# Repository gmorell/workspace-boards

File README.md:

# Gabe's Board Workspace

Kicad 7

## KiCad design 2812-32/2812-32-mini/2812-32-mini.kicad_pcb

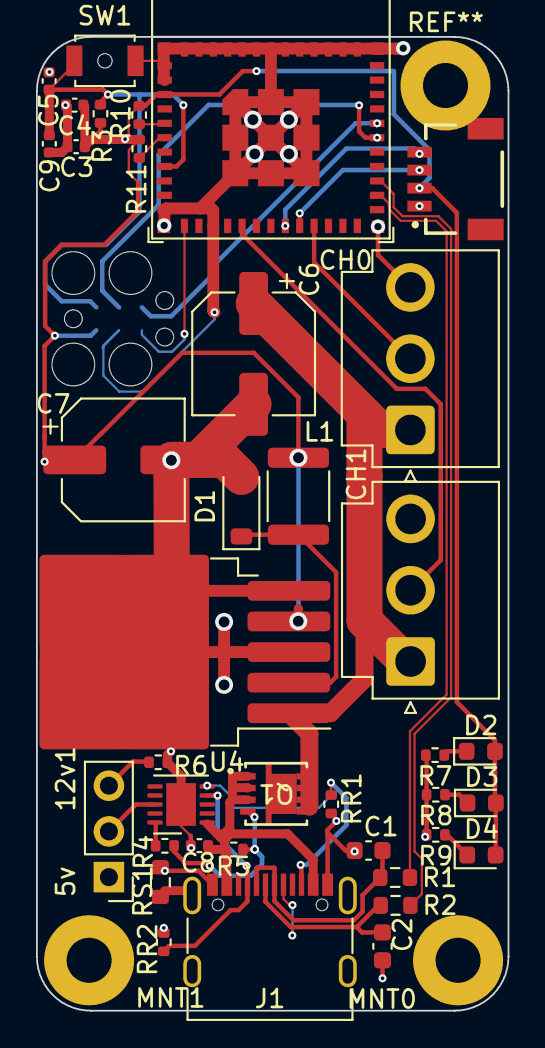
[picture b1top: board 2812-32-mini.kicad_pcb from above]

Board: 2 copper layers, 26.2 x 54.1 mm, 41 parts (1 on the bottom side), 29 nets.

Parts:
5v    12v1: VSEL; PinHeader_1x03_P2.54mm_Vertical
C1, C2: 47pF; C_0603_1608Metric
C3: 10uF; C_0402_1005Metric
C4, C9: 100nF; C_0402_1005Metric
C5, C8: 1uF; C_0402_1005Metric
C6: 100uF 50v; CP_Elec_6.3x5.3
C7: 330uF 16V; CP_Elec_6.3x7.7
CH0: CH0; JST_VH_B3P-VH-B_1x03_P3.96mm_Vertical
CH1: CH1; JST_VH_B3P-VH-B_1x03_P3.96mm_Vertical
D1: D_Schottky; D_SOD-123
D2, D3, D4: LED; LED_0603_1608Metric
J1: USB-C; USB_C_Receptacle_G-Switch_GT-USB-7010ASV
J2: I2C_STANDARDQWIIC; JST04_1MM_RA
L1: 330uH; L_1812_4532Metric
MNT0, MNT1: MountingHole_2.5mm_Pad
PROG1: TC2030-IDC_ESP; Tag-Connect_TC2030-IDC-FP_2x03_P1.27mm_Vertical
Q1: SI7611DN-T1-GE3; MOSFET_0DN-T1-GE3_VIS
R1, R2: 22; R_0603_1608Metric
R3, R6, R10, R11: 10k; R_0402_1005Metric
R4: 5.1K; R_0402_1005Metric
R5: 49.9K; R_0402_1005Metric
R7, R8, R9: R_US; R_0402_1005Metric
RR1, RR2: 5.1k; R_0402_1005Metric
RS1: 33K; R_0603_1608Metric
SW1: SW_DIP_x01; SW_SPST_B3U-1000P-B
U2: ESP32-C3-MINI-1
U3: LM2575-3.3BU; TO-263-5_TabPin3
U4: HUSB238; DFN-10-1EP_3x3mm_P0.5mm_EP1.65x2.38mm

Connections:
+3.3V: C3.1, C4.1, C7.1, D2.2 (A), D3.2 (A), D4.2 (A), J2.2 (VCC), L1.2, PROG1.2 (VDD), R3.2, R10.2, R11.2, U2.3 (3V3), U3.4 (FB)
D+: R2.2, U2.27 (GPIO19/USB_D+)
D-: R1.2, U2.26 (GPIO18/USB_D-)
EN: C5.2, C9.2, PROG1.1 (EN), R3.1, SW1.1, U2.8 (EN/CHIP_PU)
GND: 5v 12v1.1, C1.2, C2.2, C3.2, C4.2, C5.1, C6.2, C7.2, C8.2, C9.1, CH0.3, CH1.3, D1.2 (A), J1.A1 (GND), J1.A12 (GND), J1.B1 (GND), J1.B12 (GND), J2.1 (GND), PROG1.4 (GND), R6.2, R7.2, R8.2, R9.2, RR1.1, RR2.1, RS1.2, SW1.2, U2.1 (GND), U2.2 (GND), U2.11 (GND), U2.14 (GND), U2.36 (GND), U2.37 (GND), U2.38 (GND), U2.39 (GND), U2.40 (GND), U2.41 (GND), U2.42 (GND), U2.43 (GND), U2.44 (GND), U2.45 (GND), U2.46 (GND), U2.47 (GND), U2.48 (GND), U2.49 (GND), U2.50 (GND), U2.51 (GND), U2.52 (GND), U2.53 (GND), U3.3 (GND), U3.5 (~ON/OFF), U4.11 (GND)
GPIO0: PROG1.6 (IO0), U2.12 (GPIO0/ADC1_CH0/XTAL_32K_P)
GPIO7: CH0.2, U2.21 (GPIO7)
GPIO10: CH1.2, U2.16 (GPIO10)
unnamed: 5v 12v1.3, R6.1
unnamed: C1.1, J1.A7 (D-), J1.B7 (D-), R1.1
unnamed: C2.1, J1.A6 (D+), J1.B6 (D+), R2.1
unnamed: D1.1 (K), L1.1, U3.2 (OUT)
unnamed: D2.1 (K), R7.1
unnamed: D3.1 (K), R8.1
unnamed: D4.1 (K), R9.1
unnamed: J1.A5 (CC1), RR2.2, U4.4 (CC1)
unnamed: J1.B5 (CC2), RR1.2, U4.5 (CC2)
unnamed: J1.S1 (SHIELD), RS1.1
unnamed: Q1.4 (G), R4.1, R5.1
unnamed: R10.1, U2.5 (GPIO2/ADC1_CH2)
unnamed: R11.1, U2.6 (GPIO3/ADC1_CH3)
unnamed: R4.2, U4.10 (GATE)
unnamed: C8.1, J1.A4 (VBUS), J1.A9 (VBUS), J1.B4 (VBUS), J1.B9 (VBUS), Q1.1 (S), Q1.2 (S), Q1.3 (S), R5.2, U4.1 (VIN)
unnamed: 5v 12v1.2, U4.8 (VSET)
RX: PROG1.3 (TX), U2.30 (GPIO20/U0RXD)
SCL1: J2.4 (SCL), U2.19 (GPIO5/ADC2_CH0)
SDA1: J2.3 (SDA), U2.20 (GPIO6)
TX: PROG1.5 (RX), U2.31 (GPIO21/U0TXD)
VDC: C6.1, CH0.1, CH1.1, Q1.5 (D), Q1.6 (D), Q1.7 (D), Q1.8 (D), U3.1 (VIN)

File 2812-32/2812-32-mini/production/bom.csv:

Designator,Footprint,Quantity,Value,LCSC Part #
5v    12v1,PinHeader_1x03_P2.54mm_Vertical,1,VSEL,C20607074
"C1, C2",0603,2,47pF,C1671
C3,0402,1,10uF,C15525
"C4, C9",0402,2,100nF,C307331
"C5, C8",0402,2,1uF,C20539426
C6,CP_Elec_6.3x5.3,1,100uF 50v,C5354996
C7,CP_Elec_6.3x7.7,1,330uF 16V,C2980164
CH0,JST_VH_B3P-VH-B_1x03_P3.96mm_Vertical,1,CH0,C265360
CH1,JST_VH_B3P-VH-B_1x03_P3.96mm_Vertical,1,CH1,C265360
D1,D_SOD-123,1,D_Schottky,C437199
"D2, D3, D4",0603,3,LED,C5656657
J1,USB_C_Receptacle_G-Switch_GT-USB-7010ASV,1,USB-C,C2988369
J2,JST04_1MM_RA,1,I2C_STANDARDQWIIC,C160404
L1,1812,1,330uH,C394139
PROG1,Tag-Connect_TC2030-IDC-FP_2x03_P1.27mm_Vertical,1,TC2030-IDC_ESP,
Q1,MOSFET_0DN-T1-GE3_VIS,1,SI7611DN-T1-GE3,C141542
"R1, R2",0603,2,22,C2930077
"R10, R11, R3, R6",0402,4,10k,C25744
"R4, RR1, RR2",0402,3,5.1K,C25905
R5,0402,1,49.9K,C409918
"R7, R8, R9",0402,3,R_US,C2906961
RS1,0603,1,33K,C4216
SW1,SW_SPST_B3U-1000P-B,1,SW_DIP_x01,C231329
U2,ESP32-C3-MINI-1,1,ESP32-C3-MINI-1,C2838502
U3,TO-263-5_TabPin3,1,LM2575-3.3BU,C2977107
U4,DFN-10-1EP_3x3mm_P0.5mm_EP1.65x2.38mm,1,HUSB238,C7471904

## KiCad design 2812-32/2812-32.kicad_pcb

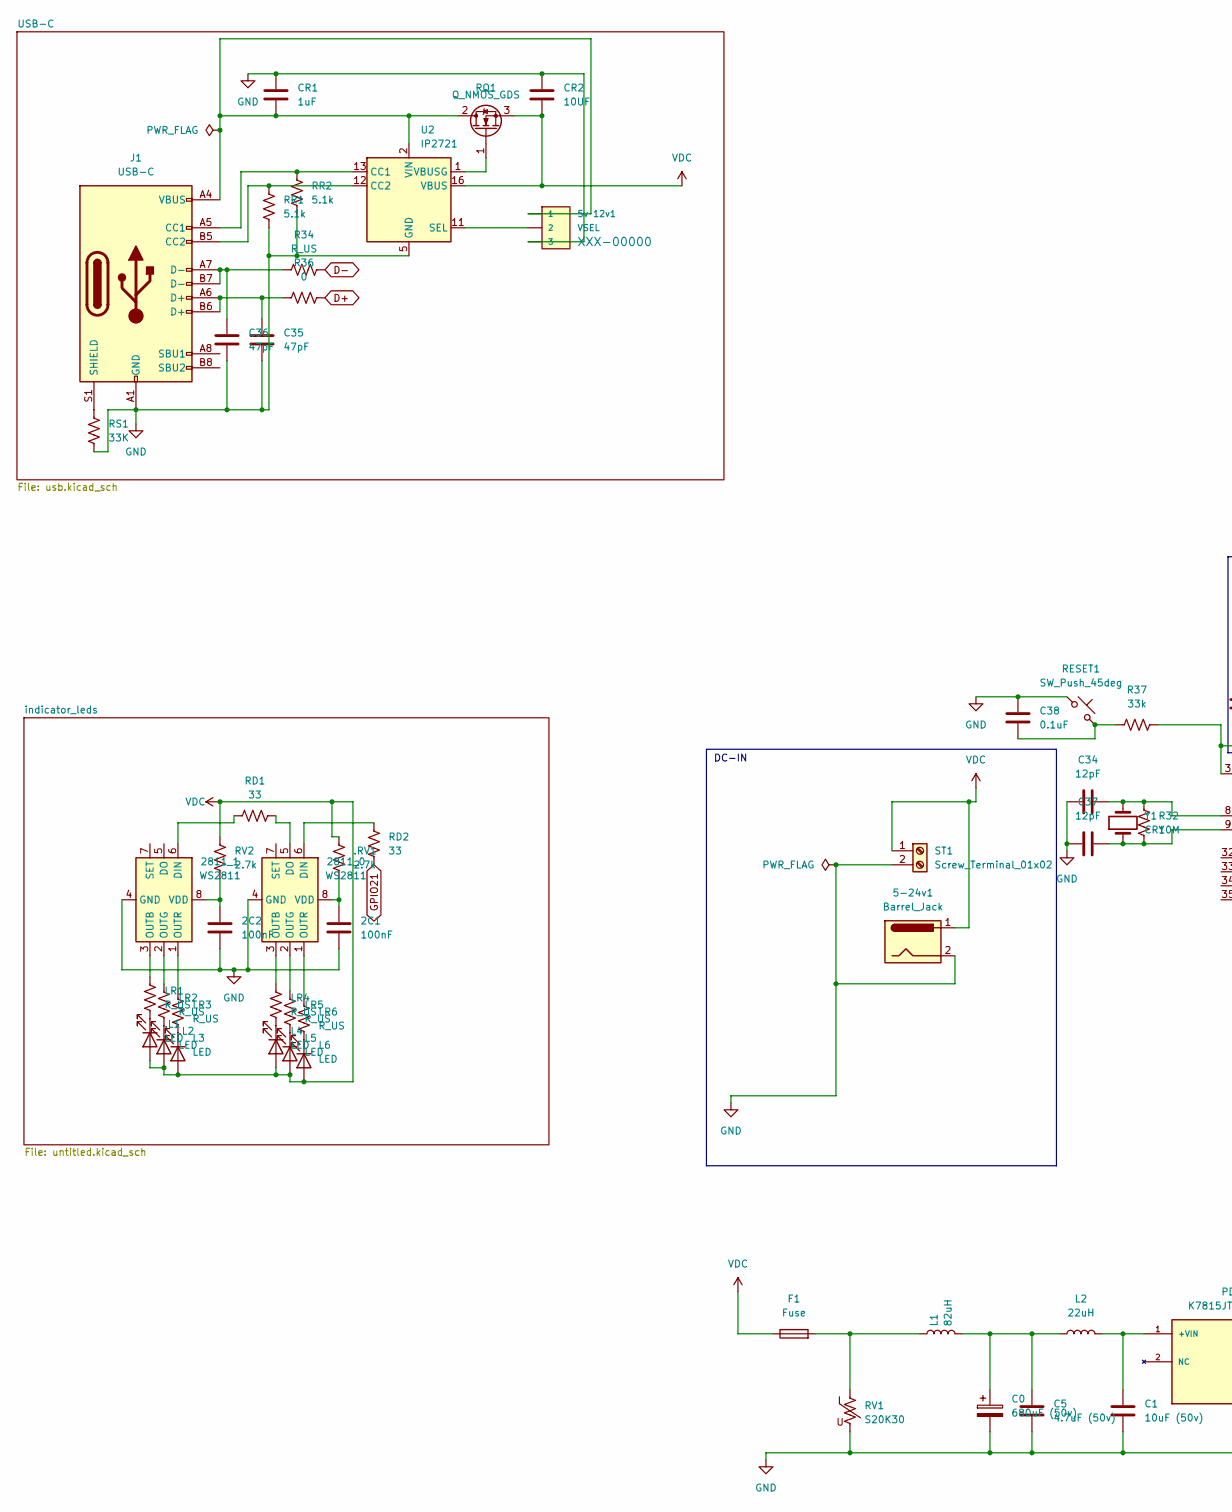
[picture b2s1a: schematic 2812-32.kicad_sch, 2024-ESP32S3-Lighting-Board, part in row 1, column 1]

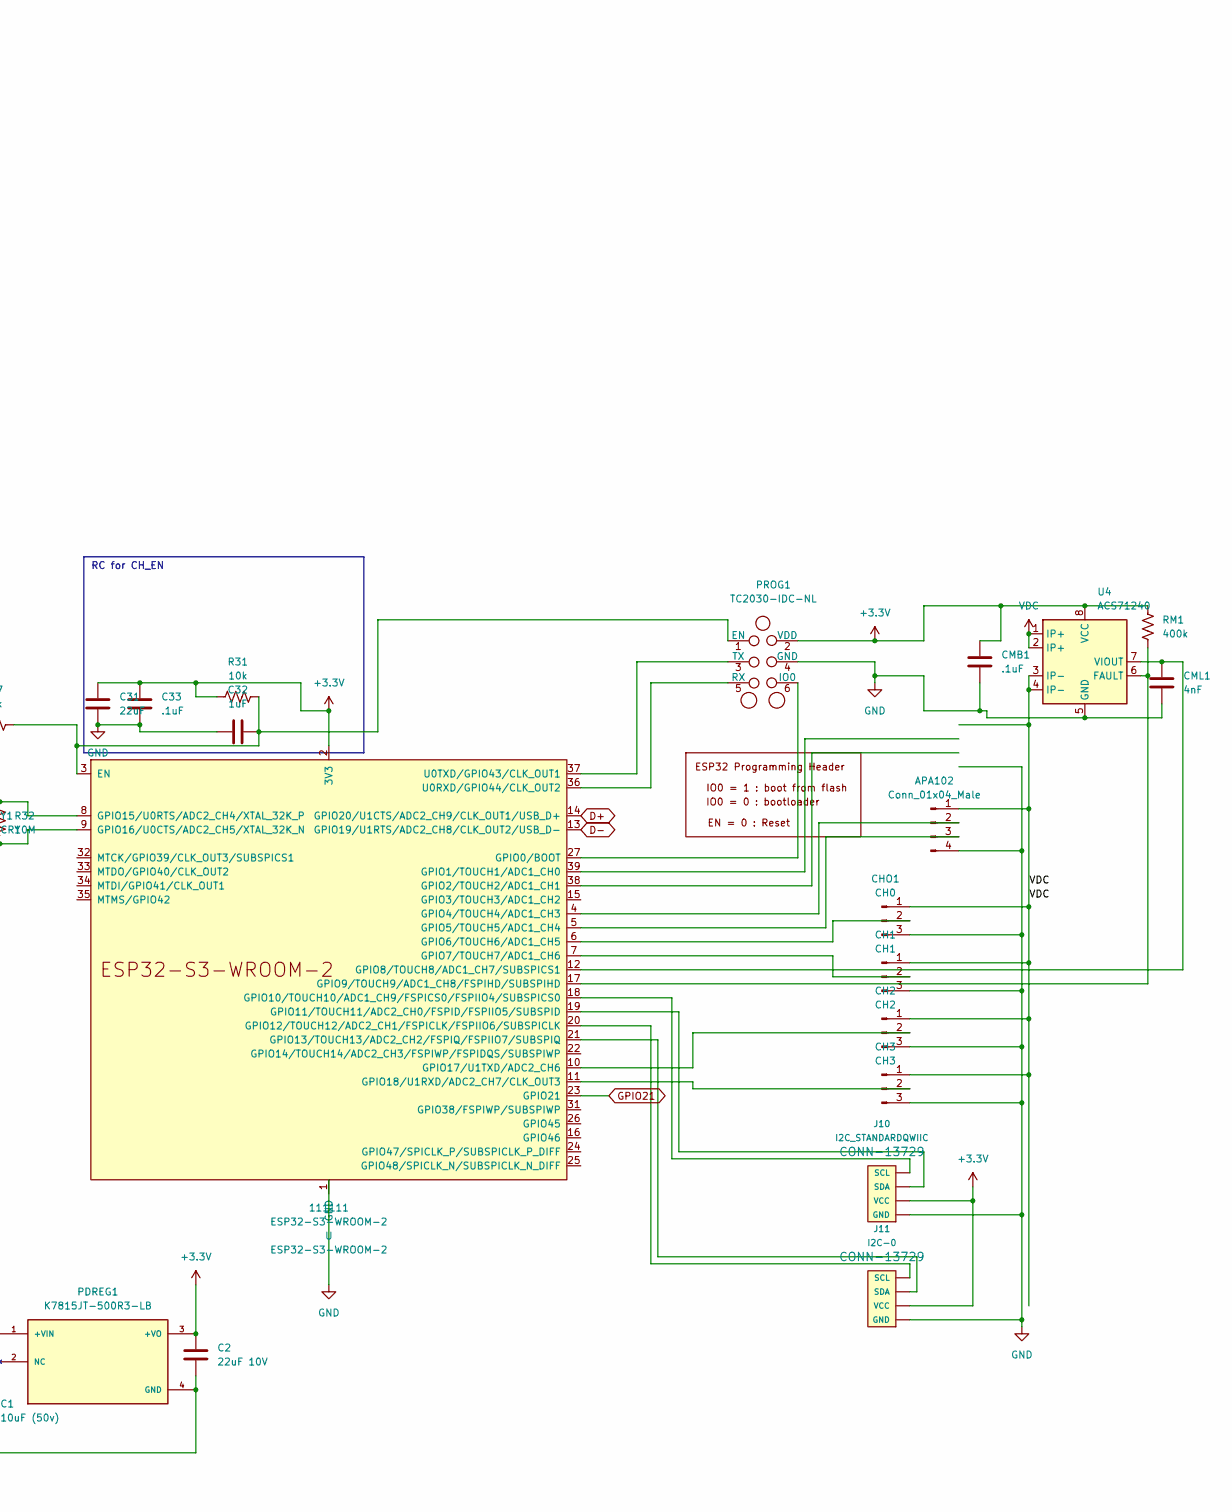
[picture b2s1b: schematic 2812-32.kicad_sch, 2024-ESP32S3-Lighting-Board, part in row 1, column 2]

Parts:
2C1, 2C2: 100nF; C_0603_1608Metric
5-24v1: Barrel_Jack; BarrelJack_CUI_PJ-063AH_Horizontal
5v    12v1: VSEL; PinHeader_1x03_P2.54mm_Vertical
2811_0, 2811_1: WS2811; SOP-8_3.9x4.9mm_P1.27mm
111111: ESP32-S3-WROOM-2
.L1, .L2: LED; LED_0603_1608Metric
.RV1: 2.7k; R_0603_1608Metric
APA102: Conn_01x04_Male; JST_VH_B4PS-VH_1x04_P3.96mm_Horizontal
C0: 680uF (50v); C_0603_1608Metric
C1: 10uF (50v); C_0603_1608Metric
C2: 22uF 10V; C_0603_1608Metric
C5: 4.7uF (50v); C_0603_1608Metric
C31: 22uF; C_0402_1005Metric
C32: 1uF; C_0603_1608Metric
C33: .1uF; C_0603_1608Metric
C34, C37: 12pF; C_0603_1608Metric
C35, C36: 47pF; C_0603_1608Metric
C38: 0.1uF; C_0603_1608Metric
CH1: CH1; JST_VH_B3PS-VH_1x03_P3.96mm_Horizontal
CH2: CH2; JST_VH_B3PS-VH_1x03_P3.96mm_Horizontal
CH3: CH3; JST_VH_B3PS-VH_1x03_P3.96mm_Horizontal
CHO1: CH0; JST_VH_B3PS-VH_1x03_P3.96mm_Horizontal
CMB1: .1uF; C_0402_1005Metric
CML1: 4nF; C_0402_1005Metric
CR1: 1uF; C_0402_1005Metric
CR2: 10UF; C_0402_1005Metric
F1: Fuse; Fuse_0603_1608Metric
J1: USB-C; USB_C_Receptacle_G-Switch_GT-USB-7010ASV
J10: I2C_STANDARDQWIIC; JST04_1MM_RA
J11: I2C-0; JST04_1MM_RA
L1: 82uH; L_0603_1608Metric
L2: 22uH; L_0603_1608Metric
L3, L4, L5, L6: LED; LED_0603_1608Metric
LR1, LR2, LR3, LR4, LR5, LR6: R_US; R_0402_1005Metric
PDREG1: K7815JT-500R3-LB; CONV_K7815JT-500R3-LB; PARTREV 2022.07.25-A/4
PROG1: TC2030-IDC_ESP; Tag-Connect_TC2030-IDC-FP_2x03_P1.27mm_Vertical
R31: 10k; R_0603_1608Metric
R32: 10M; R_0603_1608Metric
R34: R_US; R_0603_1608Metric
R36: 0; R_0603_1608Metric
R37: 33k; R_0603_1608Metric
RD1, RD2: 33; R_0603_1608Metric
RESET1: SW_Push_45deg; SW_SPST_B3U-3000P-B
RM1: 400k; R_0402_1005Metric
RQ1: Q_NMOS_GDS; SOT-23
RR1, RR2: 5.1k; R_0402_1005Metric
RS1: 33K; R_0603_1608Metric
RV1: S20K30; RV_Disc_D9mm_W3.5mm_P5mm
RV2: 2.7k; R_0603_1608Metric
ST1: Screw_Terminal_01x02; TerminalBlock_MetzConnect_Type086_RT03402HBLC_1x02_P3.81mm_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
U2: IP2721; TSSOP-16_4.4x5mm_P0.65mm
U4: ACS71240; SOIC-8_3.9x4.9mm_P1.27mm
Y1: CRY; Crystal_SMD_MicroCrystal_CC8V-T1A-2Pin_2.0x1.2mm

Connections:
+3.3V: 111111.2 (3V3), C2.1, C31.1, C33.1, CMB1.1, J10.2 (VCC), J11.2 (VCC), PDREG1.3 (+VO), PROG1.2 (VDD), R31.1, RM1.2, U4.8 (VCC)
D+: 111111.14 (GPIO20/U1CTS/ADC2_CH9/CLK_OUT1/USB_D+), R36.2
D-: 111111.13 (GPIO19/U1RTS/ADC2_CH8/CLK_OUT2/USB_D-), R34.2
GND: 2C1.2, 2C2.2, 5-24v1.2, 5v 12v1.3, 2811_0.4 (GND), 2811_1.4 (GND), 111111.1 (GND), 111111.40 (GND), 111111.41 (GND), APA102.4, C0.2, C1.2, C2.2, C5.2, C31.2, C32.1, C33.2, C34.1, C35.2, C36.2, C37.1, C38.1, CH1.3, CH2.3, CH3.3, CHO1.3, CMB1.2, CML1.2, CR1.1, CR2.1, J1.A1 (GND), J1.A12 (GND), J1.B1 (GND), J1.B12 (GND), J10.1 (GND), J11.1 (GND), PDREG1.4 (GND), PROG1.4 (GND), RESET1.1, RR1.1, RR2.1, RS1.2, RV1.2, ST1.2, U2.5 (GND), U4.5 (GND)
GPIO21: 111111.23 (GPIO21), RD2.1
unnamed: 2811_0.6 (DIN), RD2.2
unnamed: 2811_0.5 (DO), RD1.2
unnamed: 2811_0.3 (OUTB), LR4.1
unnamed: 2811_0.2 (OUTG), LR5.1
unnamed: 2811_0.1 (OUTR), LR6.1
unnamed: 2C1.1, 2811_0.8 (VDD), .RV1.2
unnamed: 2811_1.6 (DIN), RD1.1
unnamed: 2811_1.3 (OUTB), LR1.1
unnamed: 2811_1.2 (OUTG), LR2.1
unnamed: 2811_1.1 (OUTR), LR3.1
unnamed: 2C2.1, 2811_1.8 (VDD), RV2.2
unnamed: 111111.3 (EN), C32.2, PROG1.1 (EN), R31.2, R37.2
unnamed: 111111.27 (GPIO0/BOOT), PROG1.6 (IO0)
unnamed: 111111.4 (GPIO4/TOUCH4/ADC1_CH3), APA102.2
unnamed: 111111.5 (GPIO5/TOUCH5/ADC1_CH4), APA102.3
unnamed: 111111.6 (GPIO6/TOUCH6/ADC1_CH5), CHO1.2
unnamed: 111111.7 (GPIO7/TOUCH7/ADC1_CH6), CH1.2
unnamed: 111111.12 (GPIO8/TOUCH8/ADC1_CH7/SUBSPICS1), CML1.1, U4.7 (VIOUT)
unnamed: 111111.17 (GPIO9/TOUCH9/ADC1_CH8/FSPIHD/SUBSPIHD), RM1.1, U4.6 (FAULT)
unnamed: 111111.18 (GPIO10/TOUCH10/ADC1_CH9/FSPICS0/FSPIIO4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), J10.4 (SCL)
unnamed: 111111.19 (GPIO11/TOUCH11/ADC2_CH0/FSPID/FSPIIO5/S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), J10.3 (SDA)
unnamed: 111111.20 (GPIO12/TOUCH12/ADC2_CH1/FSPICLK/FSPIIO6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), J11.4 (SCL)
unnamed: 111111.21 (GPIO13/TOUCH13/ADC2_CH2/FSPIQ/FSPIIO7/S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), J11.3 (SDA)
unnamed: 111111.8 (GPIO15/U0RTS/ADC2_CH4/XTAL_32K_P), C34.2, R32.1, Y1.2
unnamed: 111111.9 (GPIO16/U0CTS/ADC2_CH5/XTAL_32K_N), C37.2, R32.2, Y1.1
unnamed: 111111.10 (GPIO17/U1TXD/ADC2_CH6), CH2.2
unnamed: 111111.11 (GPIO18/U1RXD/ADC2_CH7/CLK_OUT3), CH3.2
unnamed: 111111.36 (U0RXD/GPIO44/CLK_OUT2), PROG1.5 (RX)
unnamed: 111111.37 (U0TXD/GPIO43/CLK_OUT1), PROG1.3 (TX)
unnamed: .L1.1 (K), LR1.2
unnamed: .L2.1 (K), LR2.2
unnamed: C0.1, C5.1, L1.2, L2.1
unnamed: C35.1, J1.A6 (D+), J1.B6 (D+), R36.1
unnamed: C36.1, J1.A7 (D-), J1.B7 (D-), R34.1
unnamed: C38.2, R37.1, RESET1.2
unnamed: F1.2, L1.1, RV1.1
unnamed: J1.A5 (CC1), RR2.2, U2.13 (CC1)
unnamed: J1.B5 (CC2), RR1.2, U2.12 (CC2)
unnamed: J1.S1 (SHIELD), RS1.1
unnamed: L3.1 (K), LR3.2
unnamed: L4.1 (K), LR4.2
unnamed: L5.1 (K), LR5.2
unnamed: L6.1 (K), LR6.2
unnamed: C1.1, L2.2, PDREG1.1 (+VIN)
unnamed: 5v 12v1.1, CR1.2, J1.A4 (VBUS), J1.A9 (VBUS), J1.B4 (VBUS), J1.B9 (VBUS), RQ1.2 (D), U2.2 (VIN)
unnamed: RQ1.1 (G), U2.1 (VBUSG)
unnamed: 5v 12v1.2, U2.11 (SEL)
VDC: 5-24v1.1, .L1.2 (A), .L2.2 (A), .RV1.1, APA102.1, CH1.1, CH2.1, CH3.1, CHO1.1, CR2.2, F1.1, L3.2 (A), L4.2 (A), L5.2 (A), L6.2 (A), RQ1.3 (S), RV2.1, ST1.1, U2.16 (VBUS), U4.1 (IP+), U4.2 (IP+), U4.3 (IP-), U4.4 (IP-)

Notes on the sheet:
DC-IN
RC for CH_EN

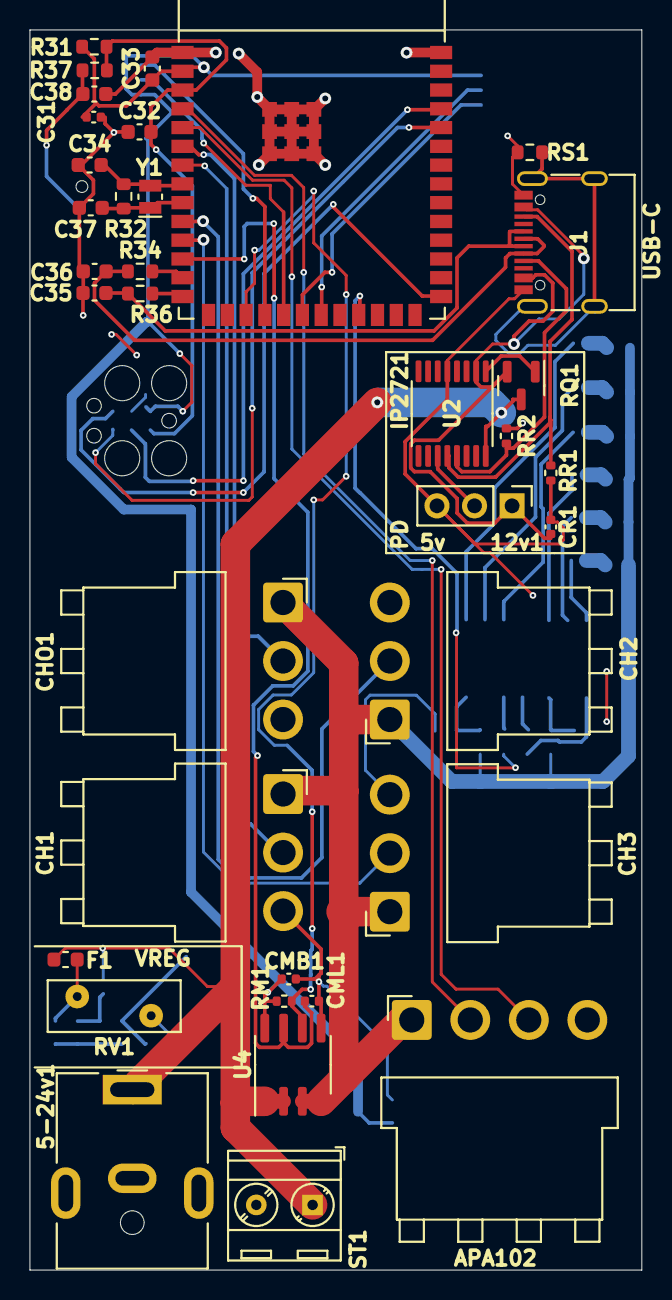
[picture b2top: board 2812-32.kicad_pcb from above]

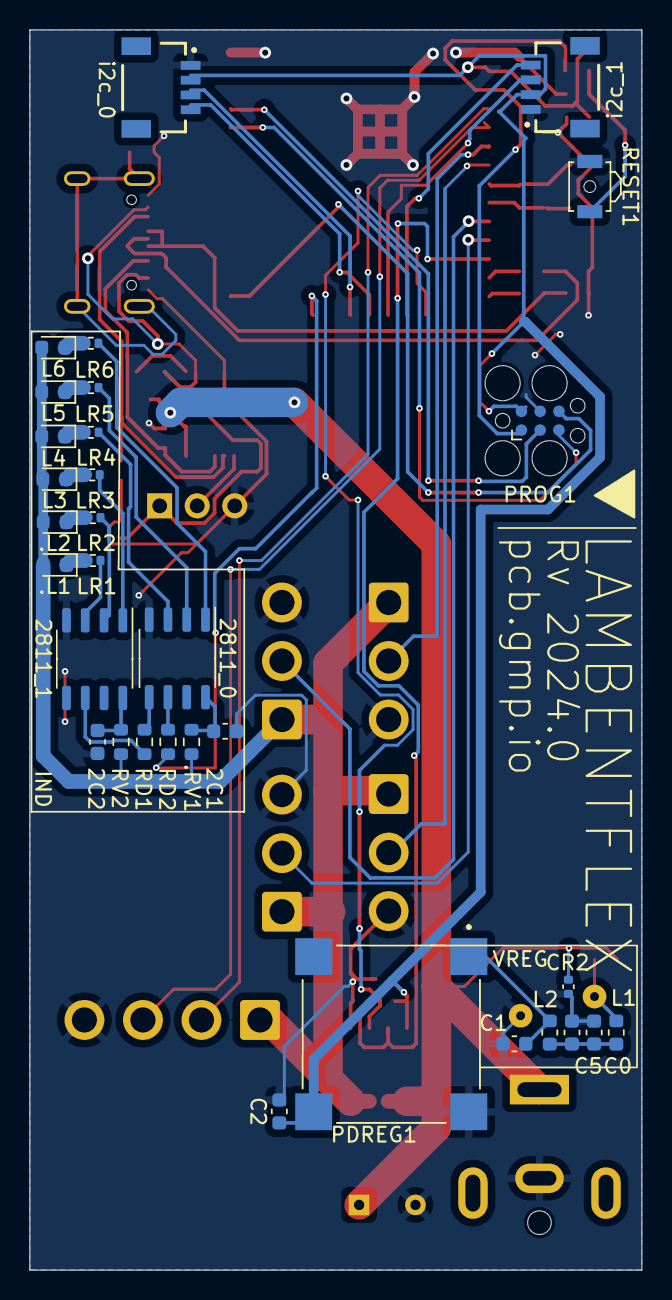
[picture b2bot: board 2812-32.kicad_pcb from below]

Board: 2 copper layers, 41.4 x 83.9 mm, 68 parts (32 on the bottom side), 53 nets.

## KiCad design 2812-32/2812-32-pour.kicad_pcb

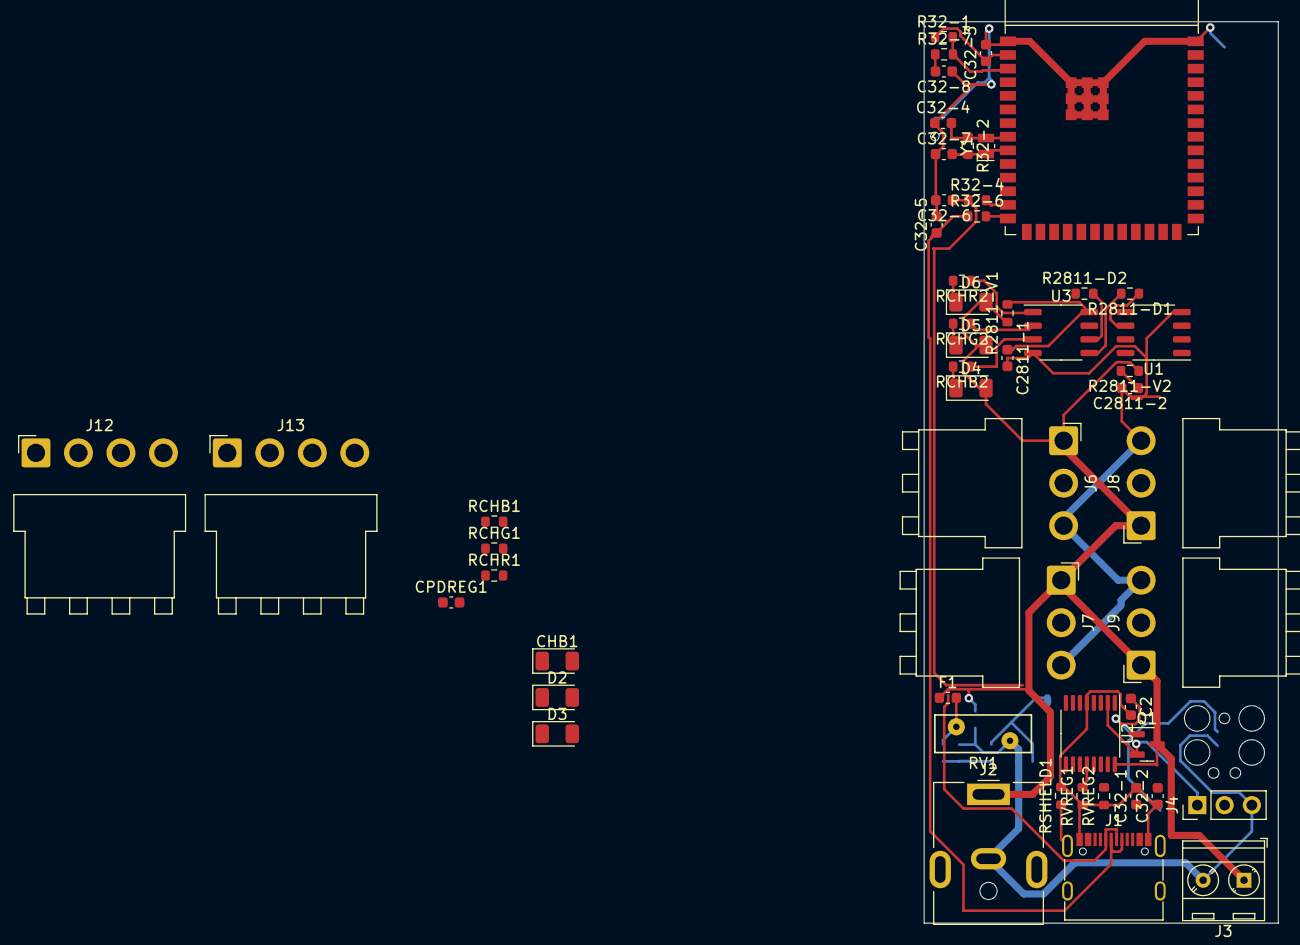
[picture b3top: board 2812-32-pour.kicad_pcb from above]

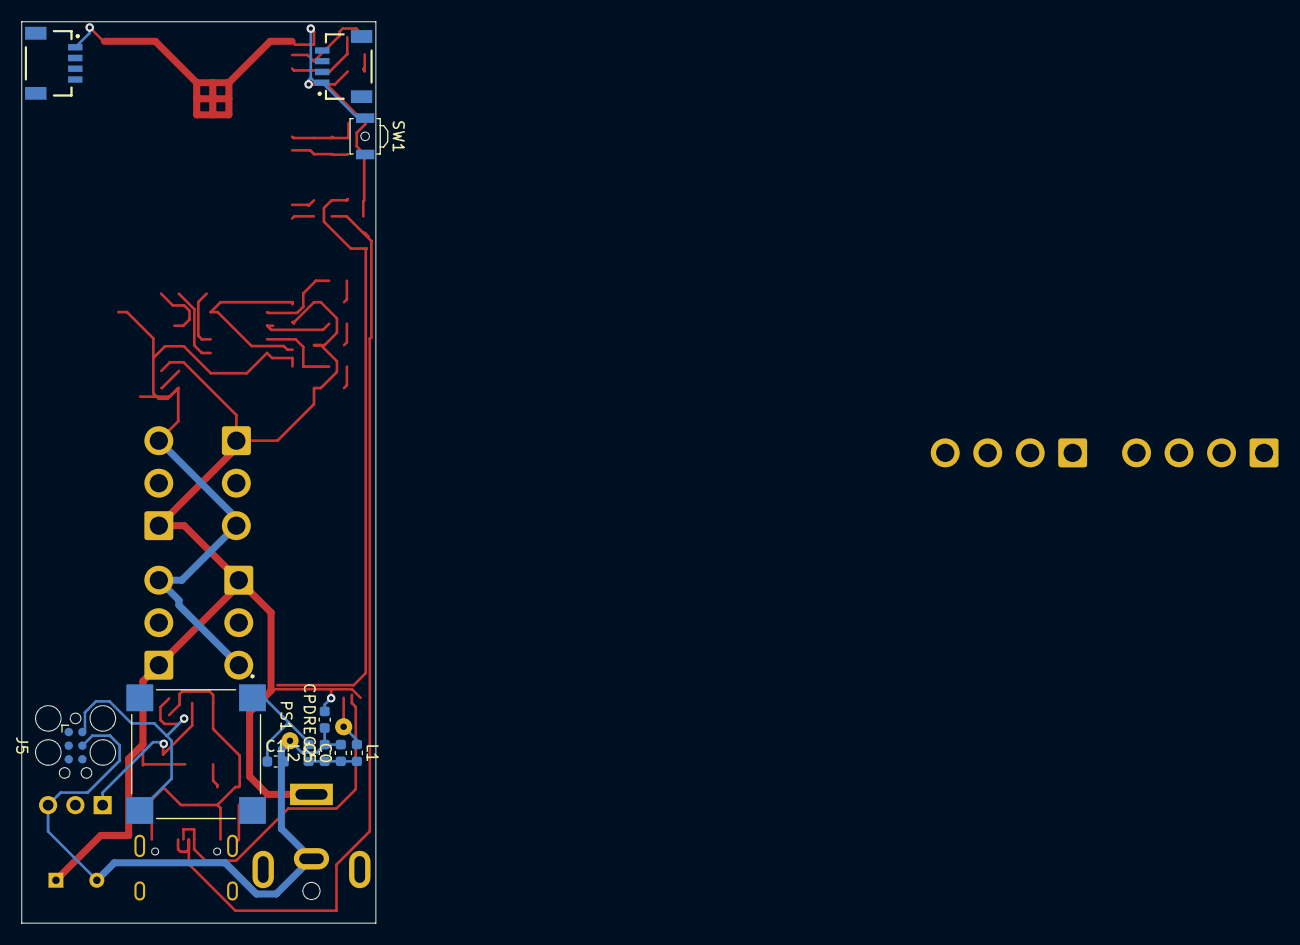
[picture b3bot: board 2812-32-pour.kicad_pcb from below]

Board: 2 copper layers, 33.0 x 84.0 mm, 65 parts (11 on the bottom side), 53 nets.

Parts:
11: ESP32-S3-WROOM-2
C0: 680uF (50v); C_0603_1608Metric
C1: 10uF (50v); C_0603_1608Metric
C2: 22uF 10V; C_0603_1608Metric
C5: 4.7uF (50v); C_0603_1608Metric
C32-1: 22uF; C_0603_1608Metric
C32-2: 1uF; C_0603_1608Metric
C32-3: .1uF; C_0603_1608Metric
C32-4, C32-7: 12pF; C_0603_1608Metric
C32-5, C32-6: 47pF; C_0603_1608Metric
C32-8: 0.1uF; C_0603_1608Metric
C2811-1, C2811-2: 100nF; C_0603_1608Metric
CHB1: LED; LED_1206_3216Metric
CPDREG1: 1uF; C_0603_1608Metric
CPDREG2: 10UF; C_0603_1608Metric
D2, D3, D4, D5, D6: LED; LED_1206_3216Metric
F1: Fuse; Fuse_0603_1608Metric
J1: USB_C_Receptacle_USB2.0; USB_C_Receptacle_G-Switch_GT-USB-7010ASV
J2: Barrel_Jack; BarrelJack_CUI_PJ-063AH_Horizontal
J3: Screw_Terminal_01x02; TerminalBlock_MetzConnect_Type086_RT03402HBLC_1x02_P3.81mm_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
J4: CONN_03; PinHeader_1x03_P2.54mm_Vertical
J5: TC2030-IDC_ESP; Tag-Connect_TC2030-IDC-FP_2x03_P1.27mm_Vertical
J6, J7, J8, J9: Conn_01x03_Male; JST_VH_B3PS-VH_1x03_P3.96mm_Horizontal
J10, J11: I2C_STANDARDQWIIC; JST04_1MM_RA
J12, J13: Conn_01x04_Male; JST_VH_B4PS-VH_1x04_P3.96mm_Horizontal
L1: 82uH; L_0603_1608Metric
L2: 22uH; L_0603_1608Metric
PS1: K7815JT-500R3-LB; CONV_K7815JT-500R3-LB
Q1: Q_NMOS_GDS; SOT-23
R32-1: 10k; R_0603_1608Metric
R32-2: 10M; R_0603_1608Metric
R32-4: R_US; R_0603_1608Metric
R32-6: 0; R_0603_1608Metric
R32-7: 33k; R_0603_1608Metric
R2811-D1, R2811-D2: 33; R_0603_1608Metric
R2811-V1, R2811-V2: 2.7k; R_0603_1608Metric
RCHB1, RCHB2: R_US; R_0603_1608Metric
RCHG1, RCHG2: R_US; R_0603_1608Metric
RCHR1, RCHR2: R_US; R_0603_1608Metric
RSHIELD1: 33K; R_0603_1608Metric
RV1: S20K30; RV_Disc_D9mm_W3.5mm_P5mm
RVREG1, RVREG2: 5.1k; R_0603_1608Metric
SW1: SW_Push_45deg; SW_SPST_B3U-3000P-B
U1, U3: WS2811; SOP-8_3.9x4.9mm_P1.27mm
U2: IP2721; TSSOP-16_4.4x5mm_P0.65mm
Y1: Crystal; Crystal_SMD_MicroCrystal_CC8V-T1A-2Pin_2.0x1.2mm

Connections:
+3.3V: 11.2 (3V3), C2.1, C32-1.1, C32-3.1, J5.2 (VDD), J10.2 (VCC), J11.2 (VCC), PS1.3 (+VO), R32-1.1
GND: 11.1 (GND), 11.40 (GND), 11.41 (GND), C0.2, C1.2, C2.2, C5.2, C32-1.2, C32-2.1, C32-3.2, C32-4.1, C32-5.2, C32-6.2, C32-7.1, C32-8.1, C2811-1.2, C2811-2.2, CPDREG1.1, CPDREG2.1, J1.A1 (GND), J1.A12 (GND), J1.B1 (GND), J1.B12 (GND), J2.2, J3.2, J4.3, J5.4 (GND), J6.3, J7.3, J8.3, J9.3, J10.1 (GND), J11.1 (GND), J12.4, J13.4, PS1.4 (GND), RSHIELD1.2, RV1.2, RVREG1.1, RVREG2.1, SW1.1, U1.4 (GND), U2.5 (GND), U3.4 (GND)
unnamed: 11.3 (EN), C32-2.2, J5.1 (EN), R32-1.2, R32-7.2
unnamed: 11.27 (GPIO0/BOOT), J5.6 (IO0)
unnamed: 11.39 (GPIO1/TOUCH1/ADC1_CH0), J12.2
unnamed: 11.38 (GPIO2/TOUCH2/ADC1_CH1), J12.3
unnamed: 11.4 (GPIO4/TOUCH4/ADC1_CH3), J13.2
unnamed: 11.5 (GPIO5/TOUCH5/ADC1_CH4), J13.3
unnamed: 11.6 (GPIO6/TOUCH6/ADC1_CH5), J6.2
unnamed: 11.7 (GPIO7/TOUCH7/ADC1_CH6), J7.2
unnamed: 11.18 (GPIO10/TOUCH10/ADC1_CH9/FSPICS0/FSPIIO4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), J10.4 (SCL)
unnamed: 11.19 (GPIO11/TOUCH11/ADC2_CH0/FSPID/FSPIIO5/S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), J10.3 (SDA)
unnamed: 11.20 (GPIO12/TOUCH12/ADC2_CH1/FSPICLK/FSPIIO6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), J11.4 (SCL)
unnamed: 11.21 (GPIO13/TOUCH13/ADC2_CH2/FSPIQ/FSPIIO7/S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), J11.3 (SDA)
unnamed: 11.8 (GPIO15/U0RTS/ADC2_CH4/XTAL_32K_P), C32-4.2, R32-2.1, Y1.2
unnamed: 11.9 (GPIO16/U0CTS/ADC2_CH5/XTAL_32K_N), C32-7.2, R32-2.2, Y1.1
unnamed: 11.10 (GPIO17/U1TXD/ADC2_CH6), J8.2
unnamed: 11.11 (GPIO18/U1RXD/ADC2_CH7/CLK_OUT3), J9.2
unnamed: 11.13 (GPIO19/U1RTS/ADC2_CH8/CLK_OUT2/USB_D-), R32-4.2
unnamed: 11.14 (GPIO20/U1CTS/ADC2_CH9/CLK_OUT1/USB_D+), R32-6.2
unnamed: 11.23 (GPIO21), R2811-D2.1
unnamed: 11.36 (U0RXD/GPIO44/CLK_OUT2), J5.5 (RX)
unnamed: 11.37 (U0TXD/GPIO43/CLK_OUT1), J5.3 (TX)
unnamed: C0.1, C5.1, L1.2, L2.1
unnamed: C32-5.1, J1.A6 (D+), J1.B6 (D+), R32-6.1
unnamed: C32-6.1, J1.A7 (D-), J1.B7 (D-), R32-4.1
unnamed: C32-8.2, R32-7.1, SW1.2
unnamed: CHB1.1 (K), RCHB1.2
unnamed: D2.1 (K), RCHG1.2
unnamed: D3.1 (K), RCHR1.2
unnamed: D4.1 (K), RCHB2.2
unnamed: D5.1 (K), RCHG2.2
unnamed: D6.1 (K), RCHR2.2
unnamed: F1.2, L1.1, RV1.1
unnamed: J1.A5 (CC1), RVREG2.2, U2.13 (CC1)
unnamed: J1.B5 (CC2), RVREG1.2, U2.12 (CC2)
unnamed: J1.S1 (SHIELD), RSHIELD1.1
unnamed: C1.1, L2.2, PS1.1 (+VIN)
unnamed: CPDREG1.2, J1.A4 (VBUS), J1.A9 (VBUS), J1.B4 (VBUS), J1.B9 (VBUS), J4.1, Q1.2 (D), U2.2 (VIN)
unnamed: Q1.1 (G), U2.1 (VBUSG)
unnamed: R2811-D1.1, U1.6 (DIN)
unnamed: RCHB1.1, U1.3 (OUTB)
unnamed: RCHG1.1, U1.2 (OUTG)
unnamed: RCHR1.1, U1.1 (OUTR)
unnamed: C2811-2.1, R2811-V2.2, U1.8 (VDD)
unnamed: J4.2, U2.11 (SEL)
unnamed: R2811-D2.2, U3.6 (DIN)
unnamed: R2811-D1.2, U3.5 (DO)
unnamed: RCHB2.1, U3.3 (OUTB)
unnamed: RCHG2.1, U3.2 (OUTG)
unnamed: RCHR2.1, U3.1 (OUTR)
unnamed: C2811-1.1, R2811-V1.2, U3.8 (VDD)
VDC: CHB1.2 (A), CPDREG2.2, D2.2 (A), D3.2 (A), D4.2 (A), D5.2 (A), D6.2 (A), F1.1, J2.1, J3.1, J6.1, J7.1, J8.1, J9.1, J12.1, J13.1, Q1.3 (S), R2811-V1.1, R2811-V2.1, U2.16 (VBUS)

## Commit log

2024-01-03 README
2024-01-03 actually commit
2024-02-03 2812-mini-rev-1
2026-01-16 mini
